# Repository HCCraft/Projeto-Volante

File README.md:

# Projeto-Volante
Arquivos de hardware e mecanica do meu projeto de volante com ffb e arduino pro micro, todo codigo utilizado foi referente a: https://github.com/vsulako/AFFBWheel/tree/master/AFFBWheel

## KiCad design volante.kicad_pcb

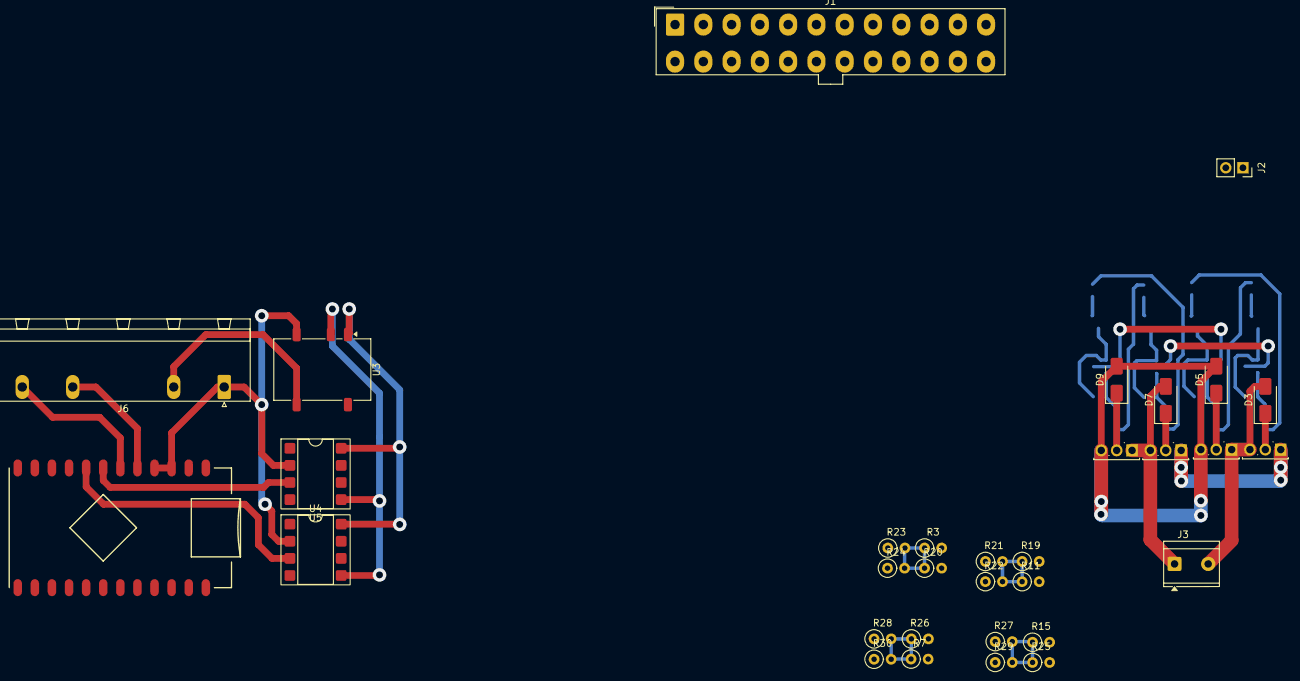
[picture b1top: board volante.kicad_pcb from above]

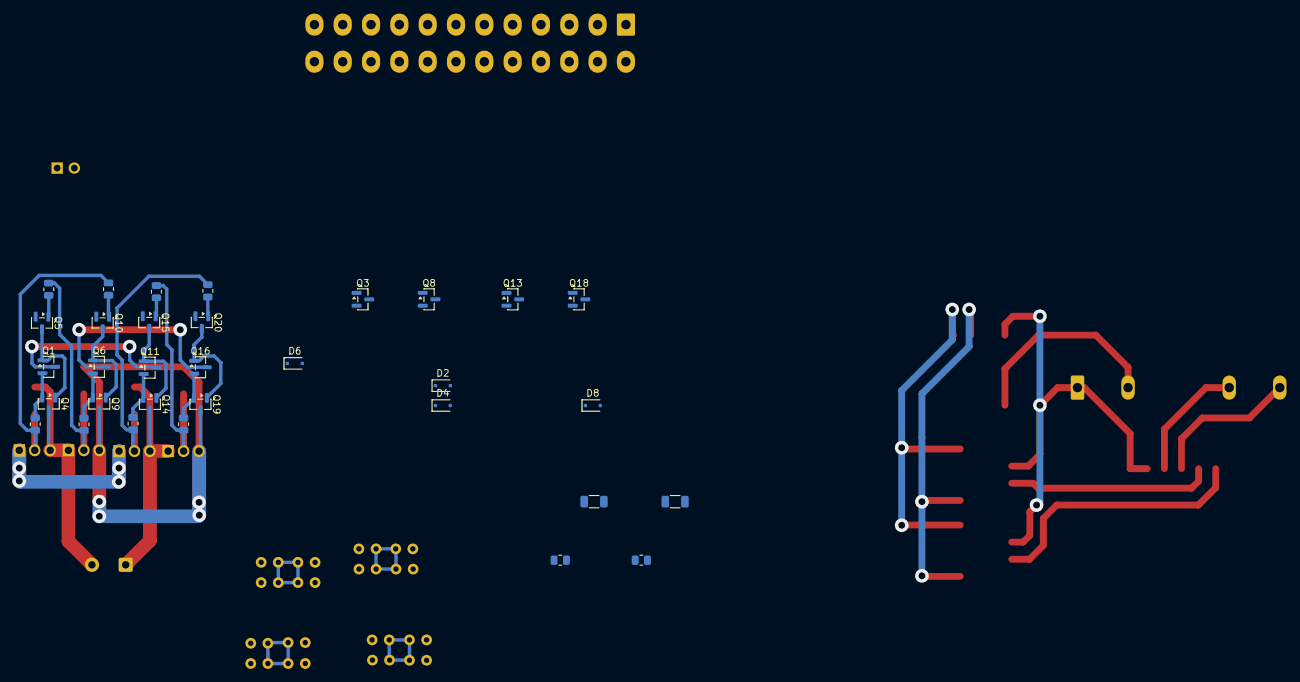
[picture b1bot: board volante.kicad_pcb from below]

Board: 2 copper layers, 64 parts (32 on the bottom side), 40 nets.

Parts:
D2, D4, D6, D8: BAS516; D_SOD-323F
D3, D5, D7, D9: SMAJ15A; D_SMA
J1: ATX-24; Molex_Mini-Fit_Jr_5566-24A_2x12_P4.20mm_Vertical
J2: Conn_01x02_Pin; PinSocket_1x02_P2.54mm_Vertical
J3: Conn_01x02_Pin; TerminalBlock_TE_282843-2_1x02_P10.16mm_Horizontal
J6: Conn_01x04; conector 4 vias 5 espaços verde
Q1, Q3, Q5, Q6, Q8, Q10, Q11, Q13, Q15, Q16, Q18, Q20: BC817; SOT-23
Q2, Q7, Q12, Q17: NMOS; TO-251-3_Vertical
Q4, Q9, Q14, Q19: BC807; SOT-23
R3, R7, R11, R15, R19, R20, R21, R22, R23, R24, R25, R26, R27, R28, R29, R30: 1K; R_Axial_DIN0207_L6.3mm_D2.5mm_P2.54mm_Vertical
R4, R8, R12, R16: 33R; R_0805_2012Metric
R5, R13: 1K; R_1206_3216Metric
R6, R10, R14, R18: 10K; R_0805_2012Metric
R9, R17: 1K; R_0805_2012Metric
U2: ProMicroC
U3: Converter_DCDC_TRACO_TES1-051x_121x_241x_Single_SMD
U4, U5: 6N137; DIP-8_W7.62mm_SMDSocket_SmallPads

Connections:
/Ponte H/meia ponte A/Gh: D7.1 (A1), Q12.2 (G), R12.2, R18.1
/Ponte H/meia ponte A/Gl: D9.1 (A1), Q17.2 (G), R14.1, R16.2
/Ponte H/meia ponte A/M: D7.2 (A2), J3.1, Q12.3 (S), Q14.3 (C), Q17.1 (D)
/Ponte H/meia ponte B/Gh: D3.1 (A1), Q2.2 (G), R4.2, R10.1
/Ponte H/meia ponte B/Gl: D5.1 (A1), Q7.2 (G), R6.1, R8.2
/Ponte H/meia ponte B/M: D3.2 (A2), J3.2, Q2.3 (S), Q4.3 (C), Q7.1 (D)
GND: D5.2 (A2), D9.2 (A2), J1.3 (GND), J1.5 (GND), J1.7 (GND), J1.15 (GND), J1.17 (GND), J1.18 (GND), J1.19 (GND), J1.24 (GND), J2.2, Q3.2 (E), Q5.2 (E), Q7.3 (S), Q8.2 (E), Q9.3 (C), Q10.2 (E), Q13.2 (E), Q15.2 (E), Q17.3 (S), Q18.2 (E), Q19.3 (C), Q20.2 (E), U3.1 (-Vin), U4.8 (VCC), U5.8 (VCC)
GNG_ISO: J6.1, U2.3 (GND), U2.4 (GND), U2.23 (GND), U3.4 (-Vout), U4.2 (A), U5.2 (A)
unnamed: D2.1 (K), Q3.1 (B), R5.2
unnamed: D4.1 (K), Q8.1 (B), R9.2
unnamed: D6.1 (K), Q13.1 (B), R13.2
unnamed: D8.1 (K), Q18.1 (B), R17.2
unnamed: J1.16 (PS_ON#), J2.1
unnamed: J6.3, U2.5 (D2)
unnamed: J6.4, U2.6 (D3)
unnamed: Q1.1 (B), Q3.3 (C), Q4.1 (B), Q5.3 (C), R3.2, R20.2
unnamed: Q1.2 (E), Q4.2 (E), R4.1
unnamed: Q5.1 (B), R6.2
unnamed: Q6.2 (E), Q9.2 (E), R8.1
unnamed: Q10.1 (B), R10.2
unnamed: Q6.1 (B), Q8.3 (C), Q9.1 (B), Q10.3 (C), R7.2, R26.2
unnamed: Q11.1 (B), Q13.3 (C), Q14.1 (B), Q15.3 (C), R11.2, R19.2
unnamed: Q11.2 (E), Q14.2 (E), R12.1
unnamed: Q15.1 (B), R14.2
unnamed: Q16.1 (B), Q18.3 (C), Q19.1 (B), Q20.3 (C), R15.2, R25.2
unnamed: Q16.2 (E), Q19.2 (E), R16.1
unnamed: Q20.1 (B), R18.2
unnamed: R11.1, R19.1, R21.2, R22.2
unnamed: R15.1, R25.1, R27.2, R29.2
unnamed: R3.1, R20.1, R23.2, R24.2
unnamed: R7.1, R26.1, R28.2, R30.2
PWM_CC: D2.2 (A), D8.2 (A), R5.1, R17.1, U5.6 (VO)
PWM_CC_ISO: U2.7 (D4/A6), U5.3 (C)
PWM_CW: D4.2 (A), D6.2 (A), R9.1, R13.1, U4.6 (VO)
PWM_CW_ISO: U2.8 (D5), U4.3 (C)
V05: J1.4 (+5V), J1.6 (+5V), J1.21 (+5V), J1.22 (+5V), J1.23 (+5V), U3.2 (+Vin), U4.5 (GND), U5.5 (GND)
V12: J1.10 (+12V), J1.11 (+12V), Q2.1 (D), Q6.3 (C), Q12.1 (D), Q16.3 (C), R27.1, R28.1, R29.1, R30.1
V12_ISO: J6.2, U3.5 (+Vout)
V22: Q1.3 (C), Q11.3 (C), R21.1, R22.1, R23.1, R24.1
V33: J1.1 (+3.3V), J1.2 (+3.3V), J1.12 (+3.3V), J1.13 (+3.3V)

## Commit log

2026-01-12 primeiro commit
2026-01-16 Criação das folhas: dc_converter_sch.kicad_sch new file: h_bridge_sch.kicad_sch
2026-01-21 alteração no circuito de ponte h e inicio da criação da PCB
2026-04-29 foi adicionado o arduino e conector de encoder na mesma placa, utilizando optacopladores recomeço do layout pcb
    Changes to be committed:
    new file: controle.kicad_sch
    modified: dc_converter_sch.kicad_sch
    modified: half_bridge.kicad_sch
    modified: volante.kicad_pcb
    modified: volante.kicad_prl
2026-06-15 alteração no circuito de controle: adição dos isoladores
    Changes to be committed:
    new file: .history
    modified: controle.kicad_sch
    modified: dc_converter_sch.kicad_sch
    modified: h_bridge_sch.kicad_sch
    modified: half_bridge.kicad_sch
